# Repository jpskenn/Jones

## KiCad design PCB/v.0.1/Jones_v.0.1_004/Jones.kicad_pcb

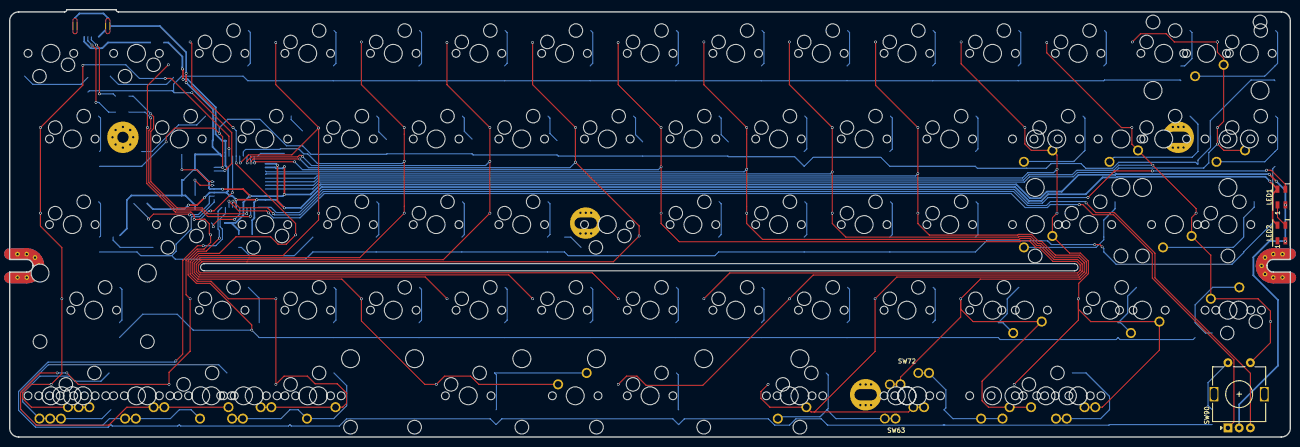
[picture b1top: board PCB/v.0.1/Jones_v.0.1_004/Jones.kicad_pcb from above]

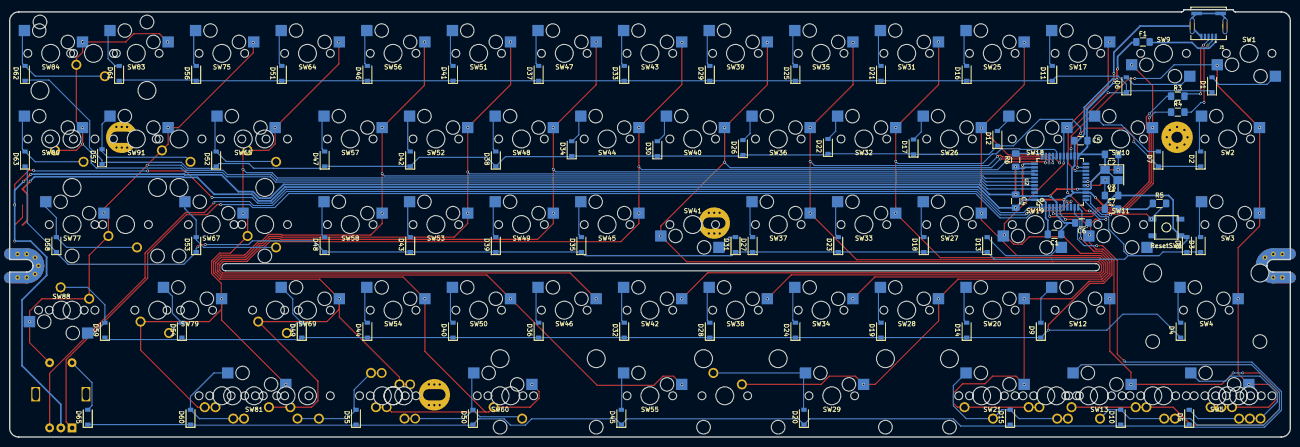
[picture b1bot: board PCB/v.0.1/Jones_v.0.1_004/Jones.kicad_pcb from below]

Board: 2 copper layers, 285.0 x 95.1 mm, 173 parts (80 on the bottom side), 99 nets.

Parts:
C1: 10uF; C_1206_3216Metric_Pad1.42x1.75mm_HandSolder
C2, C3: 22pF; C_1206_3216Metric_Pad1.42x1.75mm_HandSolder
C4, C5, C7: 0.1uF; C_1206_3216Metric_Pad1.42x1.75mm_HandSolder
C6: 1uF; C_1206_3216Metric_Pad1.42x1.75mm_HandSolder
D1, D2, D3, D4, D5, D6, D7, D8, D9, D10, D11, D12, D13, D14, D15, D16, D17, D18, D19, D20, D21, D22, D23, D24, D25, D26, D27, D28, D29, D30, D31, D32, D33, D34, D35, D36, D37, D38, D39, D40, D41, D42, D43, D44, D45, D46, D47, D48, D49, D50, D51, D52, D53, D54, D55, D56, D57, D58, D59, D60, D61, D62, D63, D65: D; D_SOD-123-Pretty
F1: 500mA; Fuse_1206_3216Metric_Pad1.42x1.75mm_HandSolder
J1: UX60SC-MB-5S8; HIROSE_UX60SC-MB-5S8
LED1, LED2: SK6812MINI; LED_SK6812MINI_PLCC4_3.5x3.5mm_P1.75mm
R3, R4: 22; R_1206_3216Metric_Pad1.42x1.75mm_HandSolder
R5, R6: 10k; R_1206_3216Metric_Pad1.42x1.75mm_HandSolder
ResetSW1: 5.2x5.2mm; SKQG-1155865
SW1, SW2, SW3, SW5, SW9, SW10, SW11, SW12, SW13, SW17, SW18, SW19, SW20, SW21, SW25, SW26, SW27, SW28, SW31, SW32, SW33, SW34, SW35, SW36, SW37, SW38, SW39, SW40, SW41, SW42, SW43, SW44, SW45, SW46, SW47, SW48, SW49, SW50, SW51, SW52, SW53, SW54, SW56, SW57, SW58, SW60, SW64, SW65, SW69, SW75, SW77, SW79, SW81, SW83, SW84, SW86, SW88, SW91: SW_Push; MXOnly-1U-Hotswap
SW4, SW55: SW_Push; MXOnly-2U-Hotswap-ReversedStabilizers
SW6, SW7, SW8, SW14, SW15, SW16, SW22, SW23, SW24, SW59, SW61, SW62, SW66, SW68, SW70, SW71, SW73, SW74, SW76, SW80, SW82, SW87, SW89: SW_Push; MXOnly-1U-NoLED
SW29, SW67: SW_Push; MXOnly-2.25U-Hotswap-ReversedStabilizers
SW30: SW_Push; MXOnly-6.25U-ReversedStabilizers-NoLED
SW63, SW72: SW_Push; SW_Cherry_MX1A_1.00u_Plate
SW78: SW_Push; MXOnly-2.25U-NoLED
SW85: SW_Push; MXOnly-2U-ReversedStabilizers-NoLED
SW90: Rotary_Encoder_Switch; RotaryEncoder_Alps_EC11E-Switch_Vertical_H20mm
U2: ATmega32U4-AU; TQFP-44_10x10mm_Pitch0.8mm
Y1: 16MHz; Crystal_SMD_3225-4Pin_3.2x2.5mm_HandSoldering

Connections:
+5V: C1.2, C4.2, C5.2, C7.2, F1.1, LED1.4, LED2.4, R5.1, U2.2, U2.7, U2.14, U2.24, U2.34, U2.44
COL0: SW1.1, SW2.1, SW3.1, SW4.1, SW5.1, SW6.1, SW7.1, SW8.1, U2.25
COL1: SW9.1, SW10.1, SW11.1, SW12.1, SW13.1, SW14.1, SW15.1, SW16.1, U2.26
COL2: SW17.1, SW18.1, SW19.1, SW20.1, SW21.1, SW22.1, SW23.1, SW24.1, U2.27
COL3: SW25.1, SW26.1, SW27.1, SW28.1, SW29.1, SW30.1, U2.28
COL4: SW31.1, SW32.1, SW33.1, SW34.1, U2.29
COL5: SW35.1, SW36.1, SW37.1, SW38.1, U2.30
COL6: SW39.1, SW40.1, SW41.1, SW42.1, U2.31
COL7: SW43.1, SW44.1, SW45.1, SW46.1, U2.32
COL8: SW47.1, SW48.1, SW49.1, SW50.1, SW55.1, U2.36
COL9: SW51.1, SW52.1, SW53.1, SW54.1, SW60.1, SW61.1, SW62.1, SW63.1, U2.37
COL10: SW56.1, SW57.1, SW58.1, SW69.1, SW70.1, SW71.1, SW72.1, SW73.1, SW74.1, U2.38
COL11: SW59.1, SW64.1, SW65.1, SW66.1, SW67.1, SW68.1, SW79.1, SW80.1, SW81.1, SW82.1, U2.39
COL12: SW75.1, SW76.1, SW77.1, SW78.1, SW88.1, SW89.1, SW90.S1, SW91.1, U2.40
COL13: SW83.1, SW84.1, SW85.1, SW86.1, SW87.1, U2.41
D+: R3.1, U2.4
D-: R4.1, U2.3
GND: C1.1, C2.2, C3.2, C4.1, C5.1, C6.2, C7.1, J1.5, J1.S1, J1.S2, J1.S3, J1.S4, LED1.2, LED2.2, R6.1, ResetSW1.1, SW90.C, U2.5, U2.15, U2.23, U2.35, U2.43, Y1.2, Y1.4
LED: LED1.3, U2.1
unnamed: C2.1, U2.17, Y1.1
unnamed: C3.1, U2.16, Y1.3
unnamed: C6.1, U2.6
unnamed: D1.2, SW1.2
unnamed: D2.2, SW2.2
unnamed: D3.2, SW3.2
unnamed: D4.2, SW4.2
unnamed: D5.2, SW5.2, SW6.2, SW7.2, SW8.2
unnamed: D6.2, SW9.2
unnamed: D7.2, SW10.2
unnamed: D8.2, SW11.2
unnamed: D9.2, SW12.2
unnamed: D10.2, SW13.2, SW14.2, SW15.2, SW16.2
unnamed: D11.2, SW17.2
unnamed: D12.2, SW18.2
unnamed: D13.2, SW19.2
unnamed: D14.2, SW20.2
unnamed: D15.2, SW21.2, SW22.2, SW23.2, SW24.2
unnamed: D16.2, SW25.2
unnamed: D17.2, SW26.2
unnamed: D18.2, SW27.2
unnamed: D19.2, SW28.2
unnamed: D20.2, SW29.2, SW30.2
unnamed: D21.2, SW31.2
unnamed: D22.2, SW32.2
unnamed: D23.2, SW33.2
unnamed: D24.2, SW34.2
unnamed: D25.2, SW35.2
unnamed: D26.2, SW36.2
unnamed: D27.2, SW37.2
unnamed: D28.2, SW38.2
unnamed: D29.2, SW39.2
unnamed: D30.2, SW40.2
unnamed: D31.2, SW41.2
unnamed: D32.2, SW42.2
unnamed: D33.2, SW43.2
unnamed: D34.2, SW44.2
unnamed: D35.2, SW45.2
unnamed: D36.2, SW46.2
unnamed: D37.2, SW47.2
unnamed: D38.2, SW48.2
unnamed: D39.2, SW49.2
unnamed: D40.2, SW50.2
unnamed: D41.2, SW51.2
unnamed: D42.2, SW52.2
unnamed: D43.2, SW53.2
unnamed: D44.2, SW54.2
unnamed: D45.2, SW55.2
unnamed: D46.2, SW56.2
unnamed: D47.2, SW57.2
unnamed: D48.2, SW58.2
unnamed: D49.2, SW69.2, SW70.2
unnamed: D50.2, SW60.2, SW61.2, SW62.2, SW63.2
unnamed: D51.2, SW64.2
unnamed: D52.2, SW65.2, SW66.2
unnamed: D53.2, SW67.2, SW68.2
unnamed: D54.2, SW79.2, SW80.2
unnamed: D55.2, SW71.2, SW72.2, SW73.2, SW74.2
unnamed: D56.2, SW75.2
unnamed: D57.2, SW76.2, SW91.2
unnamed: D58.2, SW77.2, SW78.2
unnamed: D59.2, SW88.2, SW89.2
unnamed: D60.2, SW59.2, SW81.2, SW82.2
unnamed: D61.2, SW83.2
unnamed: D62.2, SW84.2, SW85.2
unnamed: D63.2, SW86.2, SW87.2
unnamed: D65.2, SW90.S2
unnamed: J1.2, R4.2
unnamed: J1.3, R3.2
unnamed: LED1.1, LED2.3
unnamed: R5.2, ResetSW1.2, U2.13
unnamed: R6.2, U2.33
RE_A: SW90.A, U2.9
RE_B: SW90.B, U2.8
ROW0: D1.1, D6.1, D11.1, D16.1, D21.1, D25.1, D29.1, D33.1, D37.1, D41.1, D46.1, D51.1, D56.1, D61.1, U2.20
ROW1: D2.1, D7.1, D12.1, D17.1, D22.1, D26.1, D30.1, D34.1, D38.1, D42.1, D47.1, D52.1, D57.1, D62.1, U2.21
ROW2: D3.1, D8.1, D13.1, D18.1, D23.1, D27.1, D31.1, D35.1, D39.1, D43.1, D48.1, D53.1, D58.1, D63.1, U2.12
ROW3: D4.1, D9.1, D14.1, D19.1, D24.1, D28.1, D32.1, D36.1, D40.1, D44.1, D49.1, D54.1, D59.1, U2.11
ROW4: D5.1, D10.1, D15.1, D20.1, D45.1, D50.1, D55.1, D60.1, D65.1, U2.10
VCC: F1.2, J1.1

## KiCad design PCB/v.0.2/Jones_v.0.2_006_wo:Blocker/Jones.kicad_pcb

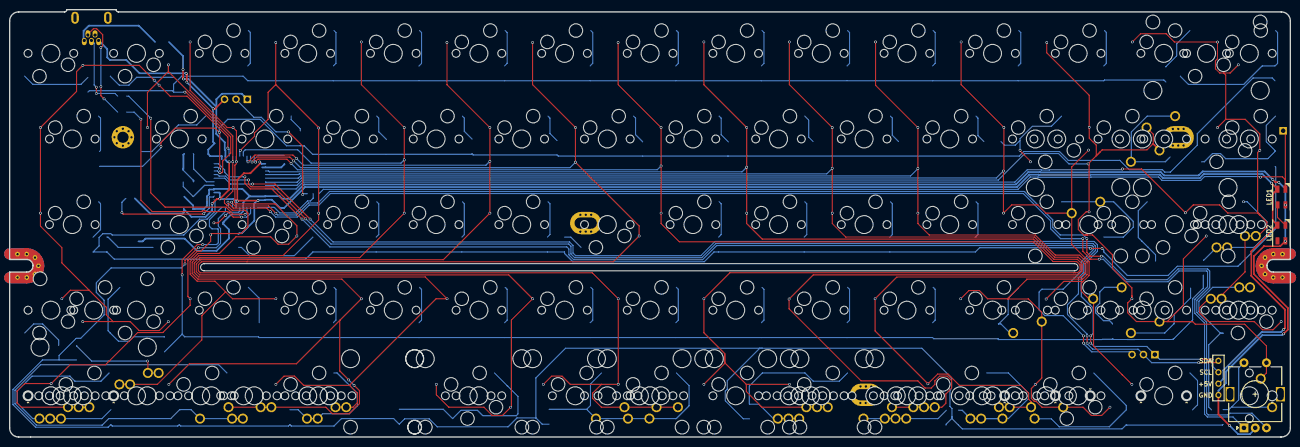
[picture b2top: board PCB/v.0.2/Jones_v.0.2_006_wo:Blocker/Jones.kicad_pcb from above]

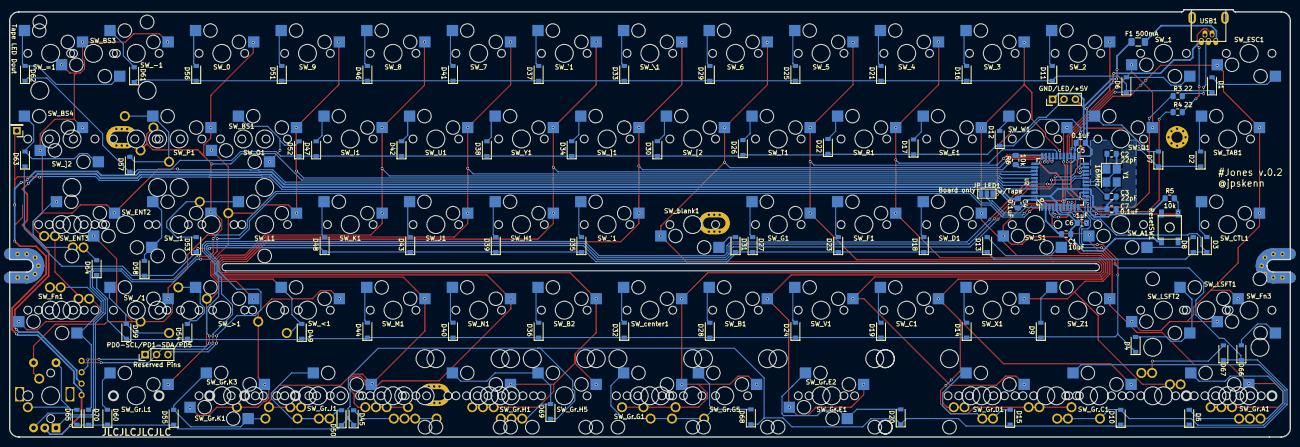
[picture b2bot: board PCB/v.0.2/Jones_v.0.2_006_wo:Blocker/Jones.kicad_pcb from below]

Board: 2 copper layers, 285.0 x 95.1 mm, 213 parts (90 on the bottom side), 110 nets.

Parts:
C1: 10uF; C_0805_2012Metric_Pad1.15x1.40mm_HandSolder
C2, C3: 22pF; C_0805_2012Metric_Pad1.15x1.40mm_HandSolder
C4, C5, C7: 0.1uF; C_0805_2012Metric_Pad1.15x1.40mm_HandSolder
C6: 1uF; C_0805_2012Metric_Pad1.15x1.40mm_HandSolder
D1, D2, D3, D4, D5, D6, D7, D8, D9, D10, D11, D12, D13, D14, D15, D16, D17, D18, D19, D20, D21, D22, D23, D24, D25, D26, D27, D28, D29, D30, D31, D32, D33, D34, D35, D36, D37, D38, D39, D40, D41, D42, D43, D44, D45, D46, D47, D48, D49, D50, D51, D52, D53, D54, D55, D56, D57, D58, D59, D60, D61, D62, D63, D64, D65, D66, D67, D68, D69, D70: D; D_SOD-123-Pretty
F1: 500mA; Fuse_1206_3216Metric_Pad1.42x1.75mm_HandSolder
H1, H2, H3, H4, H5, H6, H7, H8: MountingHole; MountingHole_2.2mm_M2
J2, J3: Conn_01x03; PinHeader_1x03_P2.54mm_Vertical
J4: Conn_01x01; PinHeader_1x01_P2.54mm_Vertical
JP_LED1: SolderJumper_3_Open; SolderJumper-3_P1.3mm_Open_Pad1.0x1.5mm_NumberLabels
LED1, LED2: SK6812MINI; LED_SK6812MINI_PLCC4_3.5x3.5mm_P1.75mm
OL1: OLED/TB; OLED_1side
R3, R4: 22; R_0805_2012Metric_Pad1.15x1.40mm_HandSolder
R5, R6: 10k; R_0805_2012Metric_Pad1.15x1.40mm_HandSolder
ResetSW1: 5.2x5.2mm; SKQG-1155865
SW_0, SW_1, SW_2, SW_3, SW_4, SW_5, SW_6, SW_7, SW_8, SW_9: SW_Push; MXOnly-1U-Hotswap
SW_'1: SW_Push; MXOnly-1U-Hotswap
SW_'2: SW_Push; MXOnly-1U-NoLED
SW_'3: SW_Push; MXOnly-1.25U-NoLED
SW_-1: SW_Push; MXOnly-1U-Hotswap
SW_/1: SW_Push; MXOnly-1U-Hotswap
SW_/2: SW_Push; MXOnly-1U-NoLED
SW_;1: SW_Push; MXOnly-1U-Hotswap
SW_<1: SW_Push; MXOnly-1U-Hotswap
SW_<2: SW_Push; MXOnly-1.75U-NoLED
SW_=1: SW_Push; MXOnly-1U-Hotswap
SW_>1: SW_Push; MXOnly-1U-Hotswap
SW_A1: SW_Push; MXOnly-1U-Hotswap
SW_B1, SW_B2: SW_Push; MXOnly-1U-Hotswap
SW_BS1, SW_BS4: SW_Push; MXOnly-1.5U-Hotswap
SW_BS2: SW_Push; MXOnly-1.5U-NoLED
SW_BS3: SW_Push; MXOnly-2U-Hotswap-ReversedStabilizers
SW_C1: SW_Push; MXOnly-1U-Hotswap
SW_CTL1: SW_Push; MXOnly-1.5U-Hotswap
SW_D1: SW_Push; MXOnly-1U-Hotswap
SW_E1: SW_Push; MXOnly-1U-Hotswap
SW_ENT1: SW_Push; MXOnly-2.25U-ReversedStabilizers-NoLED
SW_ENT2: SW_Push; MXOnly-2.25U-Hotswap
SW_ENT3: SW_Push; MXOnly-1.25U-Hotswap
SW_ESC1: SW_Push; MXOnly-1U-Hotswap
SW_F1: SW_Push; MXOnly-1U-Hotswap
SW_Fn1, SW_Fn3: SW_Push; MXOnly-1U-Hotswap
SW_Fn2: SW_Push; MXOnly-1U-NoLED
SW_Fn4: SW_Push; MXOnly-1.25U-NoLED
SW_G1: SW_Push; MXOnly-1U-Hotswap
SW_Gr.A1: SW_Push; MXOnly-1.75U-Hotswap
SW_Gr.A2, SW_Gr.C3, SW_Gr.D3, SW_Gr.H3, SW_Gr.I4: SW_Push; MXOnly-1.5U-NoLED
SW_Gr.A3, SW_Gr.B2, SW_Gr.C2, SW_Gr.C4, SW_Gr.D2, SW_Gr.H2, SW_Gr.H4, SW_Gr.I1, SW_Gr.I2, SW_Gr.I3, SW_Gr.J3: SW_Push; MXOnly-1.25U-NoLED
SW_Gr.A4, SW_Gr.B1, SW_Gr.G4, SW_Gr.J2, SW_Gr.J4: SW_Push; MXOnly-1U-NoLED
SW_Gr.C1, SW_Gr.K3, SW_Gr.L1: SW_Push; MXOnly-1U-Hotswap
SW_Gr.D1: SW_Push; MXOnly-1.5U-Hotswap
SW_Gr.E1: SW_Push; MXOnly-2.25U-Hotswap-ReversedStabilizers
SW_Gr.E2: SW_Push; MXOnly-2U-Hotswap
SW_Gr.G1, SW_Gr.H1, SW_Gr.H5: SW_Push; MXOnly-2U-Hotswap-ReversedStabilizers
SW_Gr.G2: SW_Push; MXOnly-6.25U-NoLED
SW_Gr.G3: SW_Push; MXOnly-2.25U-NoLED
SW_Gr.G5: SW_Push; MXOnly-6.25U-Hotswap-ReversedStabilizers
SW_Gr.J1, SW_Gr.K1: SW_Push; MXOnly-1.25U-Hotswap
SW_Gr.K2: SW_Push; MXOnly-1.75U-NoLED
SW_H1: SW_Push; MXOnly-1U-Hotswap
SW_I1: SW_Push; MXOnly-1U-Hotswap
SW_J1: SW_Push; MXOnly-1U-Hotswap
SW_K1: SW_Push; MXOnly-1U-Hotswap
SW_L1: SW_Push; MXOnly-1U-Hotswap
SW_LSFT1: SW_Push; MXOnly-2U-Hotswap
SW_LSFT2: SW_Push; MXOnly-1U-Hotswap
SW_M1: SW_Push; MXOnly-1U-Hotswap
SW_N1: SW_Push; MXOnly-1U-Hotswap
SW_O1: SW_Push; MXOnly-1U-Hotswap
SW_P1: SW_Push; MXOnly-1U-Hotswap
SW_Q1: SW_Push; MXOnly-1U-Hotswap
SW_R1: SW_Push; MXOnly-1U-Hotswap
SW_R.E.1: Rotary_Encoder_Switch; RotaryEncoder_Alps_EC11E-Switch_Vertical_H20mm
SW_RSFT1: SW_Push; MXOnly-1.75U-NoLED
SW_S1: SW_Push; MXOnly-1U-Hotswap
SW_T1: SW_Push; MXOnly-1U-Hotswap
SW_TAB1: SW_Push; MXOnly-1.5U-Hotswap
SW_U1: SW_Push; MXOnly-1U-Hotswap
SW_V1: SW_Push; MXOnly-1U-Hotswap
SW_W1: SW_Push; MXOnly-1U-Hotswap
SW_X1: SW_Push; MXOnly-1U-Hotswap
SW_Y1: SW_Push; MXOnly-1U-Hotswap
SW_Z1: SW_Push; MXOnly-1U-Hotswap
SW_[1: SW_Push; MXOnly-1U-NoLED
SW_[2: SW_Push; MXOnly-1U-Hotswap
SW_\1: SW_Push; MXOnly-1U-Hotswap
SW_]1, SW_]2: SW_Push; MXOnly-1U-Hotswap
SW_`1: SW_Push; MXOnly-1U-Hotswap
SW_blank1: SW_Push; MXOnly-1U-Hotswap
SW_center1: SW_Push; MXOnly-1U-Hotswap
SW_extra1: SW_Push; MXOnly-1U-NoLED
U2: ATmega32U4-AU; TQFP-44_10x10mm_Pitch0.8mm
USB1: Molex-0548190519
Y1: 16MHz; Crystal_SMD_3225-4Pin_3.2x2.5mm_HandSoldering

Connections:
+5V: C1.2, C4.2, C5.2, C7.2, F1.1, J3.1, LED1.4, LED2.4, OL1.3, R5.1, U2.2, U2.7, U2.14, U2.24, U2.34, U2.44
COL0: SW_CTL1.1, SW_ESC1.1, SW_Fn3.1, SW_LSFT1.1, SW_LSFT2.1, SW_TAB1.1, U2.25
COL1: SW_1.1, SW_A1.1, SW_Gr.A1.1, SW_Gr.A2.1, SW_Gr.A3.1, SW_Gr.A4.1, SW_Q1.1, SW_Z1.1, U2.26
COL2: SW_2.1, SW_Gr.B1.1, SW_Gr.B2.1, SW_S1.1, SW_W1.1, SW_X1.1, U2.27
COL3: SW_3.1, SW_C1.1, SW_D1.1, SW_E1.1, SW_Gr.C1.1, SW_Gr.C2.1, SW_Gr.C3.1, SW_Gr.C4.1, U2.28
COL4: SW_4.1, SW_F1.1, SW_Gr.D1.1, SW_Gr.D2.1, SW_Gr.D3.1, SW_R1.1, SW_V1.1, U2.29
COL5: SW_5.1, SW_B1.1, SW_G1.1, SW_Gr.E1.1, SW_Gr.E2.1, SW_T1.1, U2.30
COL6: SW_6.1, SW_Gr.G1.1, SW_Gr.G2.1, SW_Gr.G3.1, SW_Gr.G4.1, SW_Gr.G5.1, SW_[2.1, SW_blank1.1, SW_center1.1, U2.31
COL7: SW_'1.1, SW_B2.1, SW_Gr.H1.1, SW_Gr.H2.1, SW_Gr.H3.1, SW_Gr.H4.1, SW_Gr.H5.1, SW_\1.1, SW_]1.1, U2.32
COL8: SW_Gr.I1.1, SW_Gr.I2.1, SW_Gr.I3.1, SW_Gr.I4.1, SW_H1.1, SW_N1.1, SW_Y1.1, SW_`1.1, U2.36
COL9: SW_7.1, SW_Gr.J1.1, SW_Gr.J2.1, SW_Gr.J3.1, SW_Gr.J4.1, SW_J1.1, SW_M1.1, SW_U1.1, U2.37
COL10: SW_8.1, SW_<1.1, SW_<2.1, SW_Gr.K1.1, SW_Gr.K2.1, SW_Gr.K3.1, SW_I1.1, SW_K1.1, U2.38
COL11: SW_9.1, SW_>1.1, SW_BS1.1, SW_ENT1.1, SW_Gr.L1.1, SW_L1.1, SW_O1.1, SW_RSFT1.1, U2.39
COL12: SW_0.1, SW_/1.1, SW_/2.1, SW_;1.1, SW_BS2.1, SW_ENT2.1, SW_P1.1, SW_R.E.1.S1, SW_[1.1, SW_extra1.1, U2.40
COL13: SW_'2.1, SW_'3.1, SW_-1.1, SW_=1.1, SW_BS3.1, SW_BS4.1, SW_ENT3.1, SW_Fn1.1, SW_Fn2.1, SW_Fn4.1, SW_]2.1, U2.41
D+: R3.1, U2.4
D-: R4.1, U2.3
GND: C1.1, C2.2, C3.2, C4.1, C5.1, C6.2, C7.1, J3.3, LED1.2, LED2.2, OL1.4, R6.1, ResetSW1.1, SW_R.E.1.C, U2.5, U2.15, U2.23, U2.35, U2.43, USB1.1, Y1.2, Y1.4
LED: JP_LED1.2, U2.1
LED_TAPE: J3.2, JP_LED1.3
unnamed: C2.1, U2.17, Y1.1
unnamed: C3.1, U2.16, Y1.3
unnamed: C6.1, U2.6
unnamed: D1.2, SW_ESC1.2
unnamed: D2.2, SW_TAB1.2
unnamed: D3.2, SW_CTL1.2
unnamed: D4.2, SW_LSFT1.2, SW_LSFT2.2
unnamed: D5.2, SW_Gr.A1.2, SW_Gr.A2.2, SW_Gr.A3.2, SW_Gr.A4.2
unnamed: D6.2, SW_1.2
unnamed: D7.2, SW_Q1.2
unnamed: D8.2, SW_A1.2
unnamed: D9.2, SW_Z1.2
unnamed: D10.2, SW_Gr.C1.2, SW_Gr.C2.2, SW_Gr.C3.2, SW_Gr.C4.2
unnamed: D11.2, SW_2.2
unnamed: D12.2, SW_W1.2
unnamed: D13.2, SW_S1.2
unnamed: D14.2, SW_X1.2
unnamed: D15.2, SW_Gr.D1.2, SW_Gr.D2.2, SW_Gr.D3.2
unnamed: D16.2, SW_3.2
unnamed: D17.2, SW_E1.2
unnamed: D18.2, SW_D1.2
unnamed: D19.2, SW_C1.2
unnamed: D20.2, SW_Gr.E1.2, SW_Gr.E2.2
unnamed: D21.2, SW_4.2
unnamed: D22.2, SW_R1.2
unnamed: D23.2, SW_F1.2
unnamed: D24.2, SW_V1.2
unnamed: D25.2, SW_5.2
unnamed: D26.2, SW_T1.2
unnamed: D27.2, SW_G1.2
unnamed: D28.2, SW_B1.2
unnamed: D29.2, SW_6.2
unnamed: D30.2, SW_[2.2
unnamed: D31.2, SW_blank1.2
unnamed: D32.2, SW_center1.2
unnamed: D33.2, SW_\1.2
unnamed: D34.2, SW_]1.2
unnamed: D35.2, SW_'1.2
unnamed: D36.2, SW_B2.2
unnamed: D37.2, SW_`1.2
unnamed: D38.2, SW_Y1.2
unnamed: D39.2, SW_H1.2
unnamed: D40.2, SW_N1.2
unnamed: D41.2, SW_7.2
unnamed: D42.2, SW_U1.2
unnamed: D43.2, SW_J1.2
unnamed: D44.2, SW_M1.2
unnamed: D45.2, SW_Gr.I1.2, SW_Gr.I2.2, SW_Gr.I3.2, SW_Gr.I4.2
unnamed: D46.2, SW_8.2
unnamed: D47.2, SW_I1.2
unnamed: D48.2, SW_K1.2
unnamed: D49.2, SW_<1.2, SW_<2.2
unnamed: D50.2, SW_Gr.J1.2, SW_Gr.J2.2, SW_Gr.J3.2, SW_Gr.J4.2
unnamed: D51.2, SW_9.2
unnamed: D52.2, SW_BS1.2, SW_O1.2
unnamed: D53.2, SW_ENT1.2, SW_L1.2
unnamed: D54.2, SW_>1.2, SW_RSFT1.2
unnamed: D55.2, SW_Gr.K1.2, SW_Gr.K2.2, SW_Gr.K3.2
unnamed: D56.2, SW_0.2
unnamed: D57.2, SW_BS2.2, SW_P1.2, SW_[1.2
unnamed: D58.2, SW_;1.2, SW_ENT2.2
unnamed: D59.2, SW_/1.2, SW_/2.2
unnamed: D60.2, SW_Gr.L1.2
unnamed: D61.2, SW_-1.2
unnamed: D62.2, SW_=1.2, SW_BS3.2
unnamed: D63.2, SW_BS4.2, SW_]2.2
unnamed: D64.2, SW_'2.2, SW_'3.2, SW_ENT3.2
unnamed: D66.2, SW_Fn3.2
unnamed: D67.2, SW_Gr.B1.2, SW_Gr.B2.2
unnamed: D68.2, SW_Gr.G1.2, SW_Gr.G2.2, SW_Gr.G3.2, SW_Gr.G4.2, SW_Gr.G5.2
unnamed: D69.2, SW_Gr.H1.2, SW_Gr.H2.2, SW_Gr.H3.2, SW_Gr.H4.2, SW_Gr.H5.2
unnamed: D70.2, SW_Fn1.2, SW_Fn2.2, SW_Fn4.2
unnamed: J4.1, JP_LED1.1, LED1.3
unnamed: LED1.1, LED2.3
unnamed: R3.2, USB1.3
unnamed: R4.2, USB1.4
unnamed: R5.2, ResetSW1.2, U2.13
unnamed: R6.2, U2.33
RE_A: SW_R.E.1.A, U2.9
RE_B: SW_R.E.1.B, U2.8
RE_S2: D65.2, SW_R.E.1.S2, SW_extra1.2
ROW0: D1.1, D6.1, D11.1, D16.1, D21.1, D25.1, D29.1, D33.1, D37.1, D41.1, D46.1, D51.1, D56.1, D61.1, U2.20
ROW1: D2.1, D7.1, D12.1, D17.1, D22.1, D26.1, D30.1, D34.1, D38.1, D42.1, D47.1, D52.1, D57.1, D62.1, U2.21
ROW2: D3.1, D8.1, D13.1, D18.1, D23.1, D27.1, D31.1, D35.1, D39.1, D43.1, D48.1, D53.1, D58.1, D63.1, U2.12
ROW3: D4.1, D9.1, D14.1, D19.1, D24.1, D28.1, D32.1, D36.1, D40.1, D44.1, D49.1, D54.1, D59.1, D64.1, U2.11
ROW4: D5.1, D10.1, D15.1, D20.1, D45.1, D50.1, D55.1, D60.1, D65.1, D66.1, D67.1, D68.1, D69.1, D70.1, U2.10
Reserve_PD0-SCL: J2.1, OL1.2, U2.18
Reserve_PD1-SDA: J2.2, OL1.1, U2.19
Reserve_PD5: J2.3, U2.22
VCC: F1.2, USB1.5
